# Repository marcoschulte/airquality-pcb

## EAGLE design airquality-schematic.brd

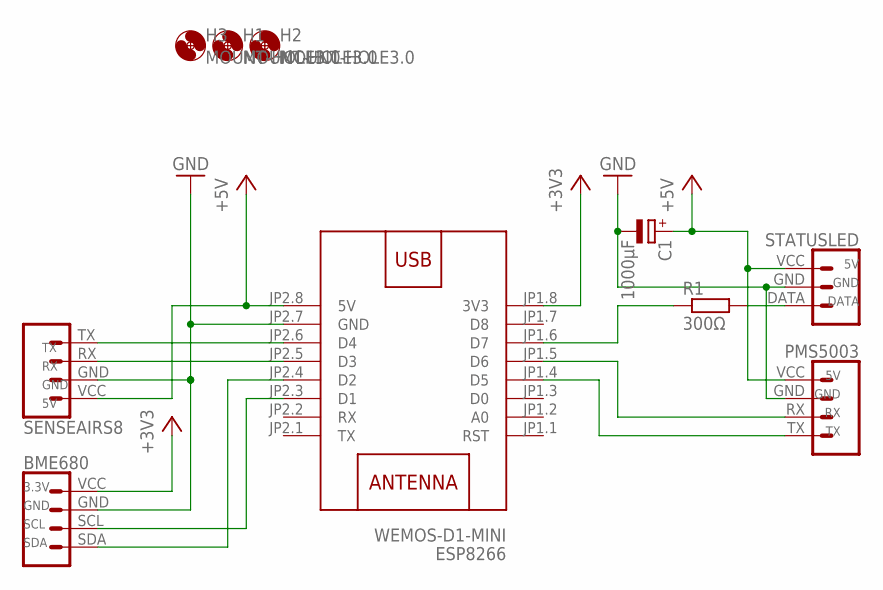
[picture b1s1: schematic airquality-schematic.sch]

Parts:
BME680: BME680
C1: 1000µF; E5-10,5
ESP8266: WEMOS-D1-MINI
H1, H2, H3: MOUNT-HOLE3.0; 3,0
PMS5003: PMS5003
R1: 300Ω; 0207/10
SENSEAIRS8: SENSEAIRS8
STATUSLED: LED

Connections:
+3V3: BME680.VCC, ESP8266.JP1.8 (3V3)
+5V: C1.+, ESP8266.JP2.8 (5V), PMS5003.VCC, SENSEAIRS8.VCC, STATUSLED.VCC
GND: BME680.GND, C1.-, ESP8266.JP2.7 (GND), PMS5003.GND, SENSEAIRS8.GND, STATUSLED.GND
unnamed: ESP8266.JP1.6 (D7), R1.1
unnamed: R1.2, STATUSLED.DATA
unnamed: ESP8266.JP2.6 (D4), SENSEAIRS8.TX
unnamed: ESP8266.JP2.5 (D3), SENSEAIRS8.RX
unnamed: BME680.SCL, ESP8266.JP2.3 (D1)
unnamed: BME680.SDA, ESP8266.JP2.4 (D2)
unnamed: ESP8266.JP1.4 (D5), PMS5003.TX
unnamed: ESP8266.JP1.5 (D6), PMS5003.RX

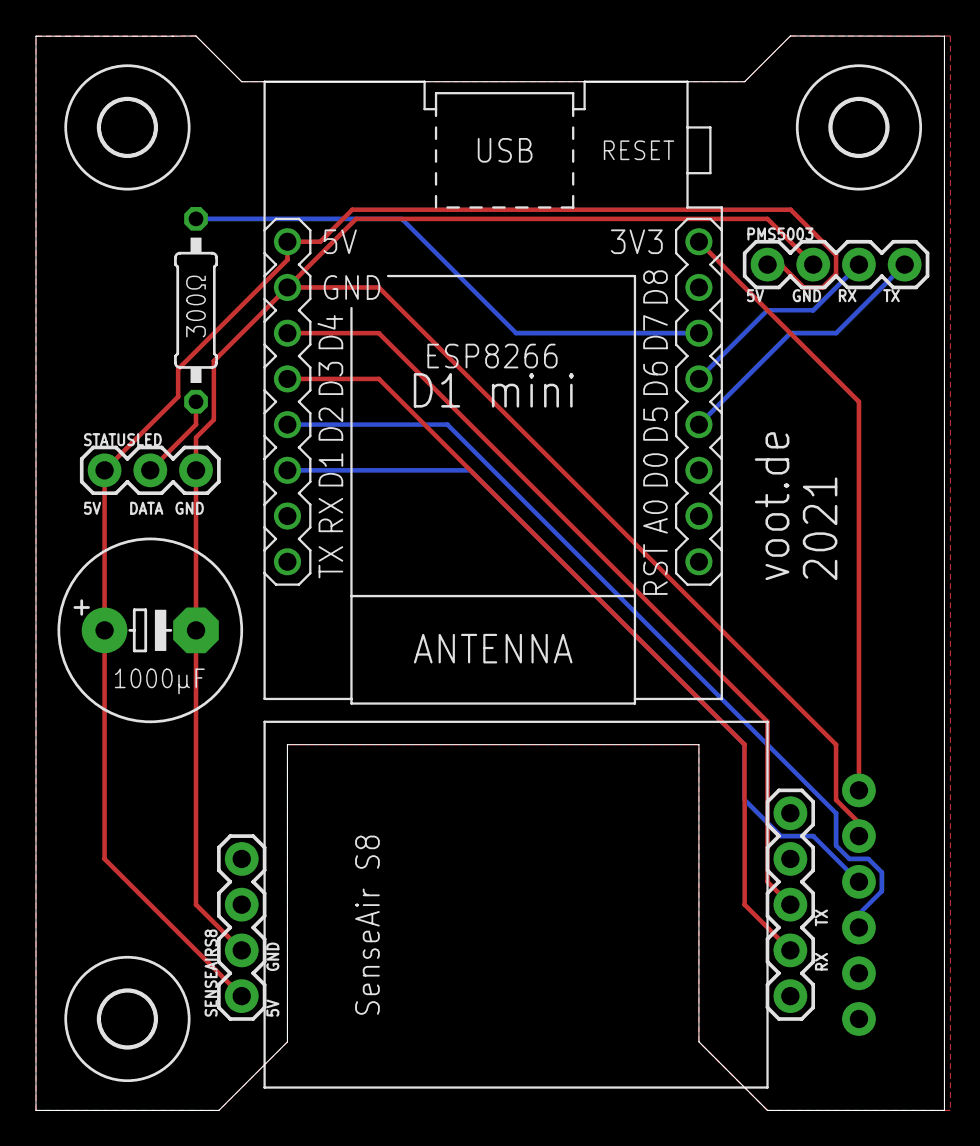
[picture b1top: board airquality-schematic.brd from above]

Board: 2 copper layers, 50.5 x 59.7 mm, 10 parts (1 on the bottom side), 11 nets.

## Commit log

2021-07-15 V1.0
